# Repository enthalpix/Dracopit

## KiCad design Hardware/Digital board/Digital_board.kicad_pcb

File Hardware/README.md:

# Dracopit
74 logic custom interactive game

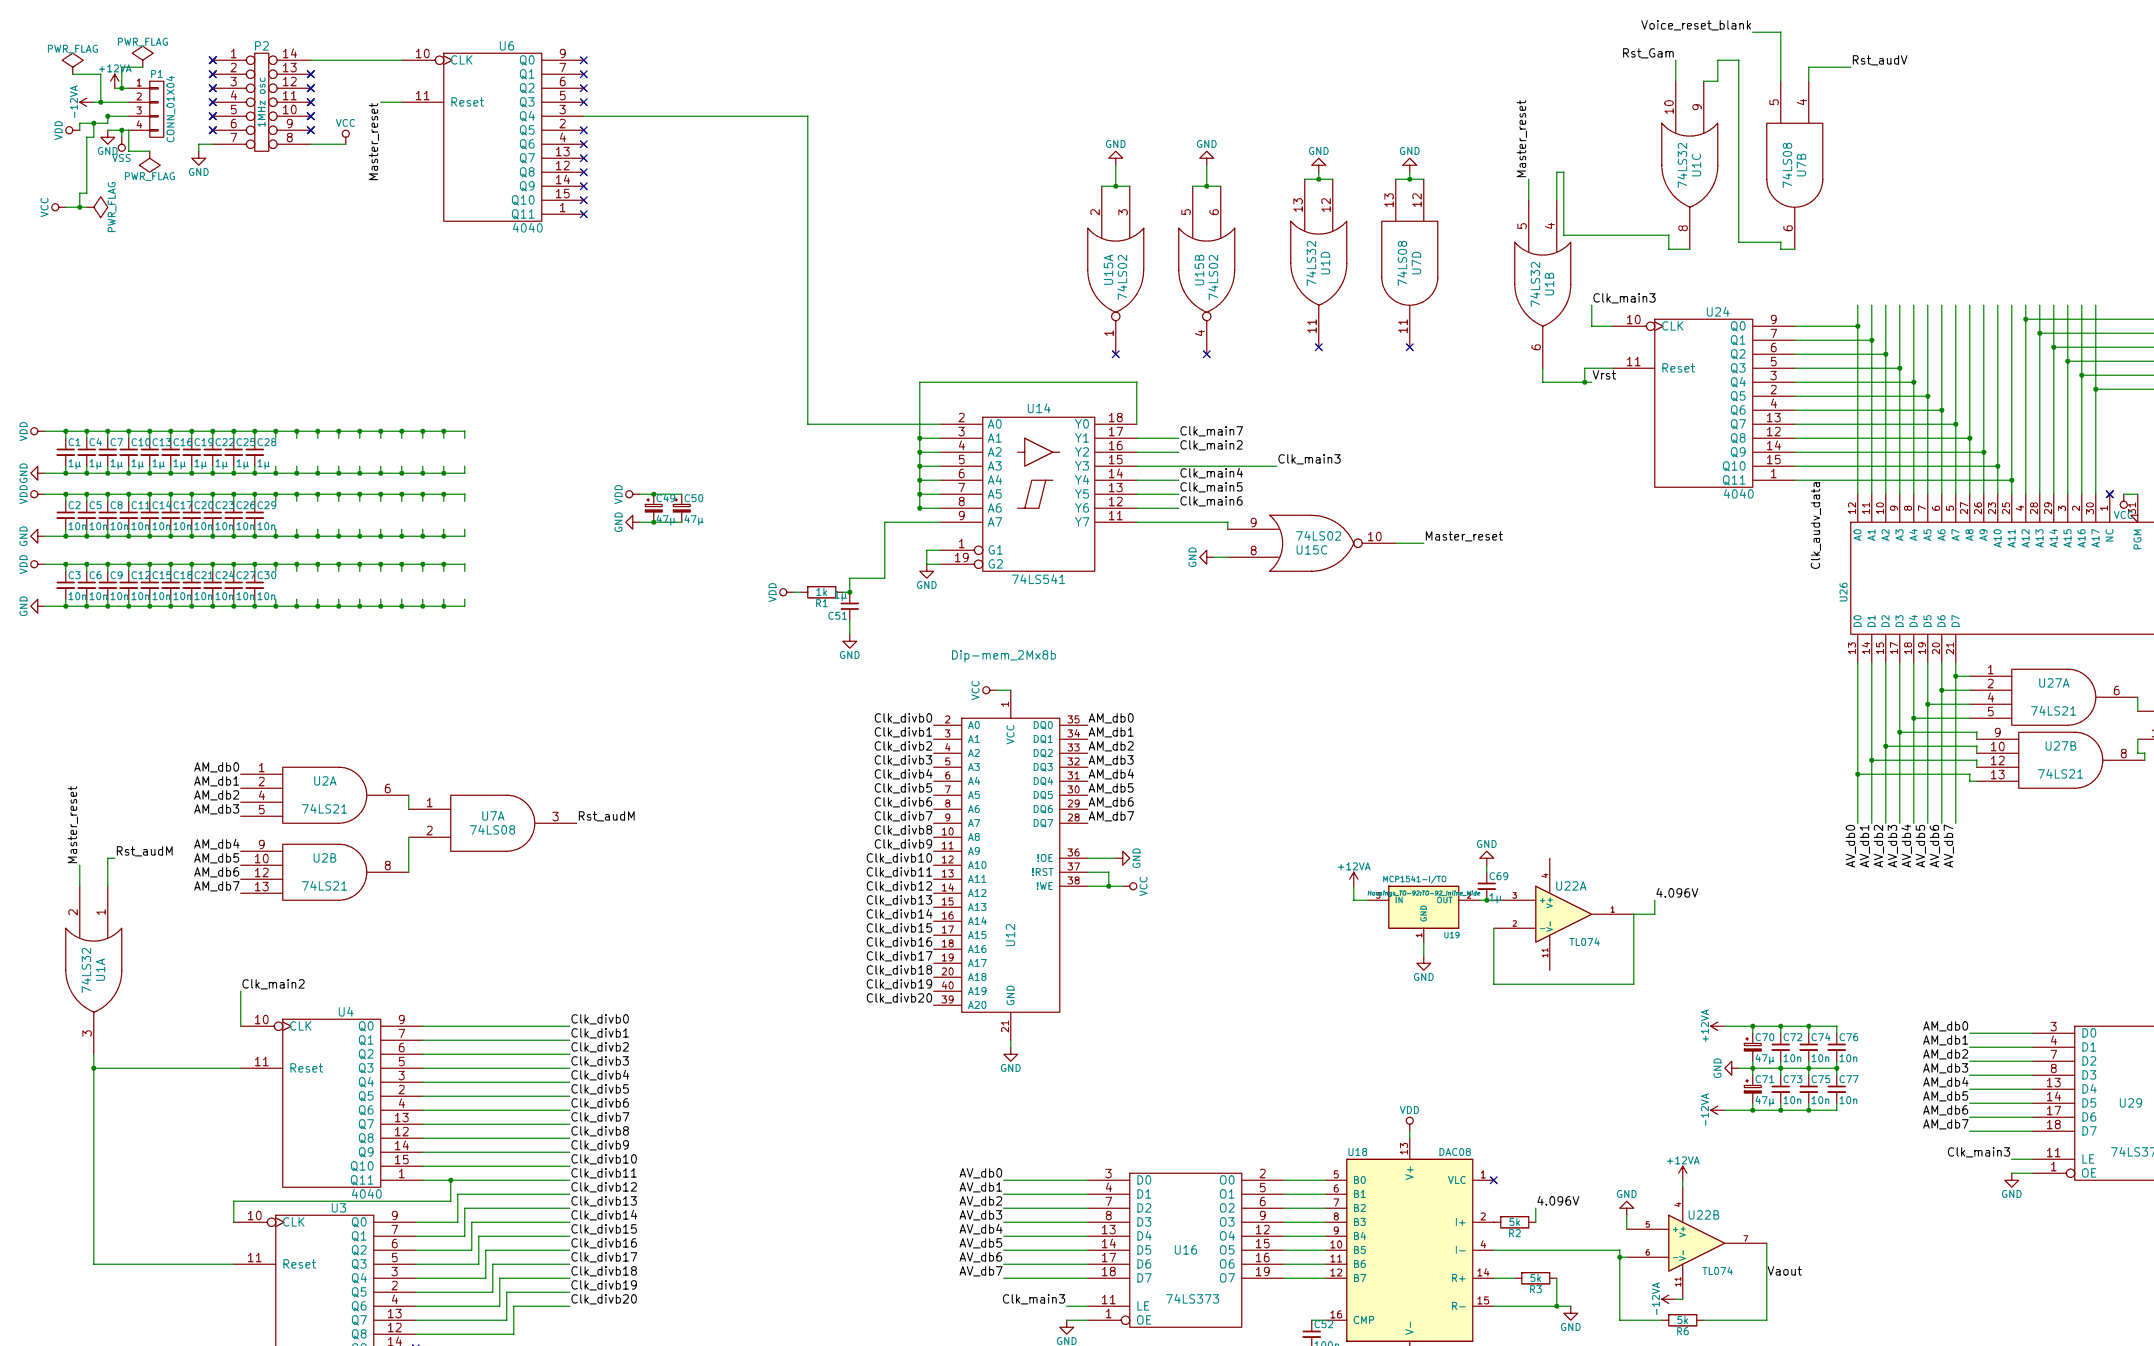
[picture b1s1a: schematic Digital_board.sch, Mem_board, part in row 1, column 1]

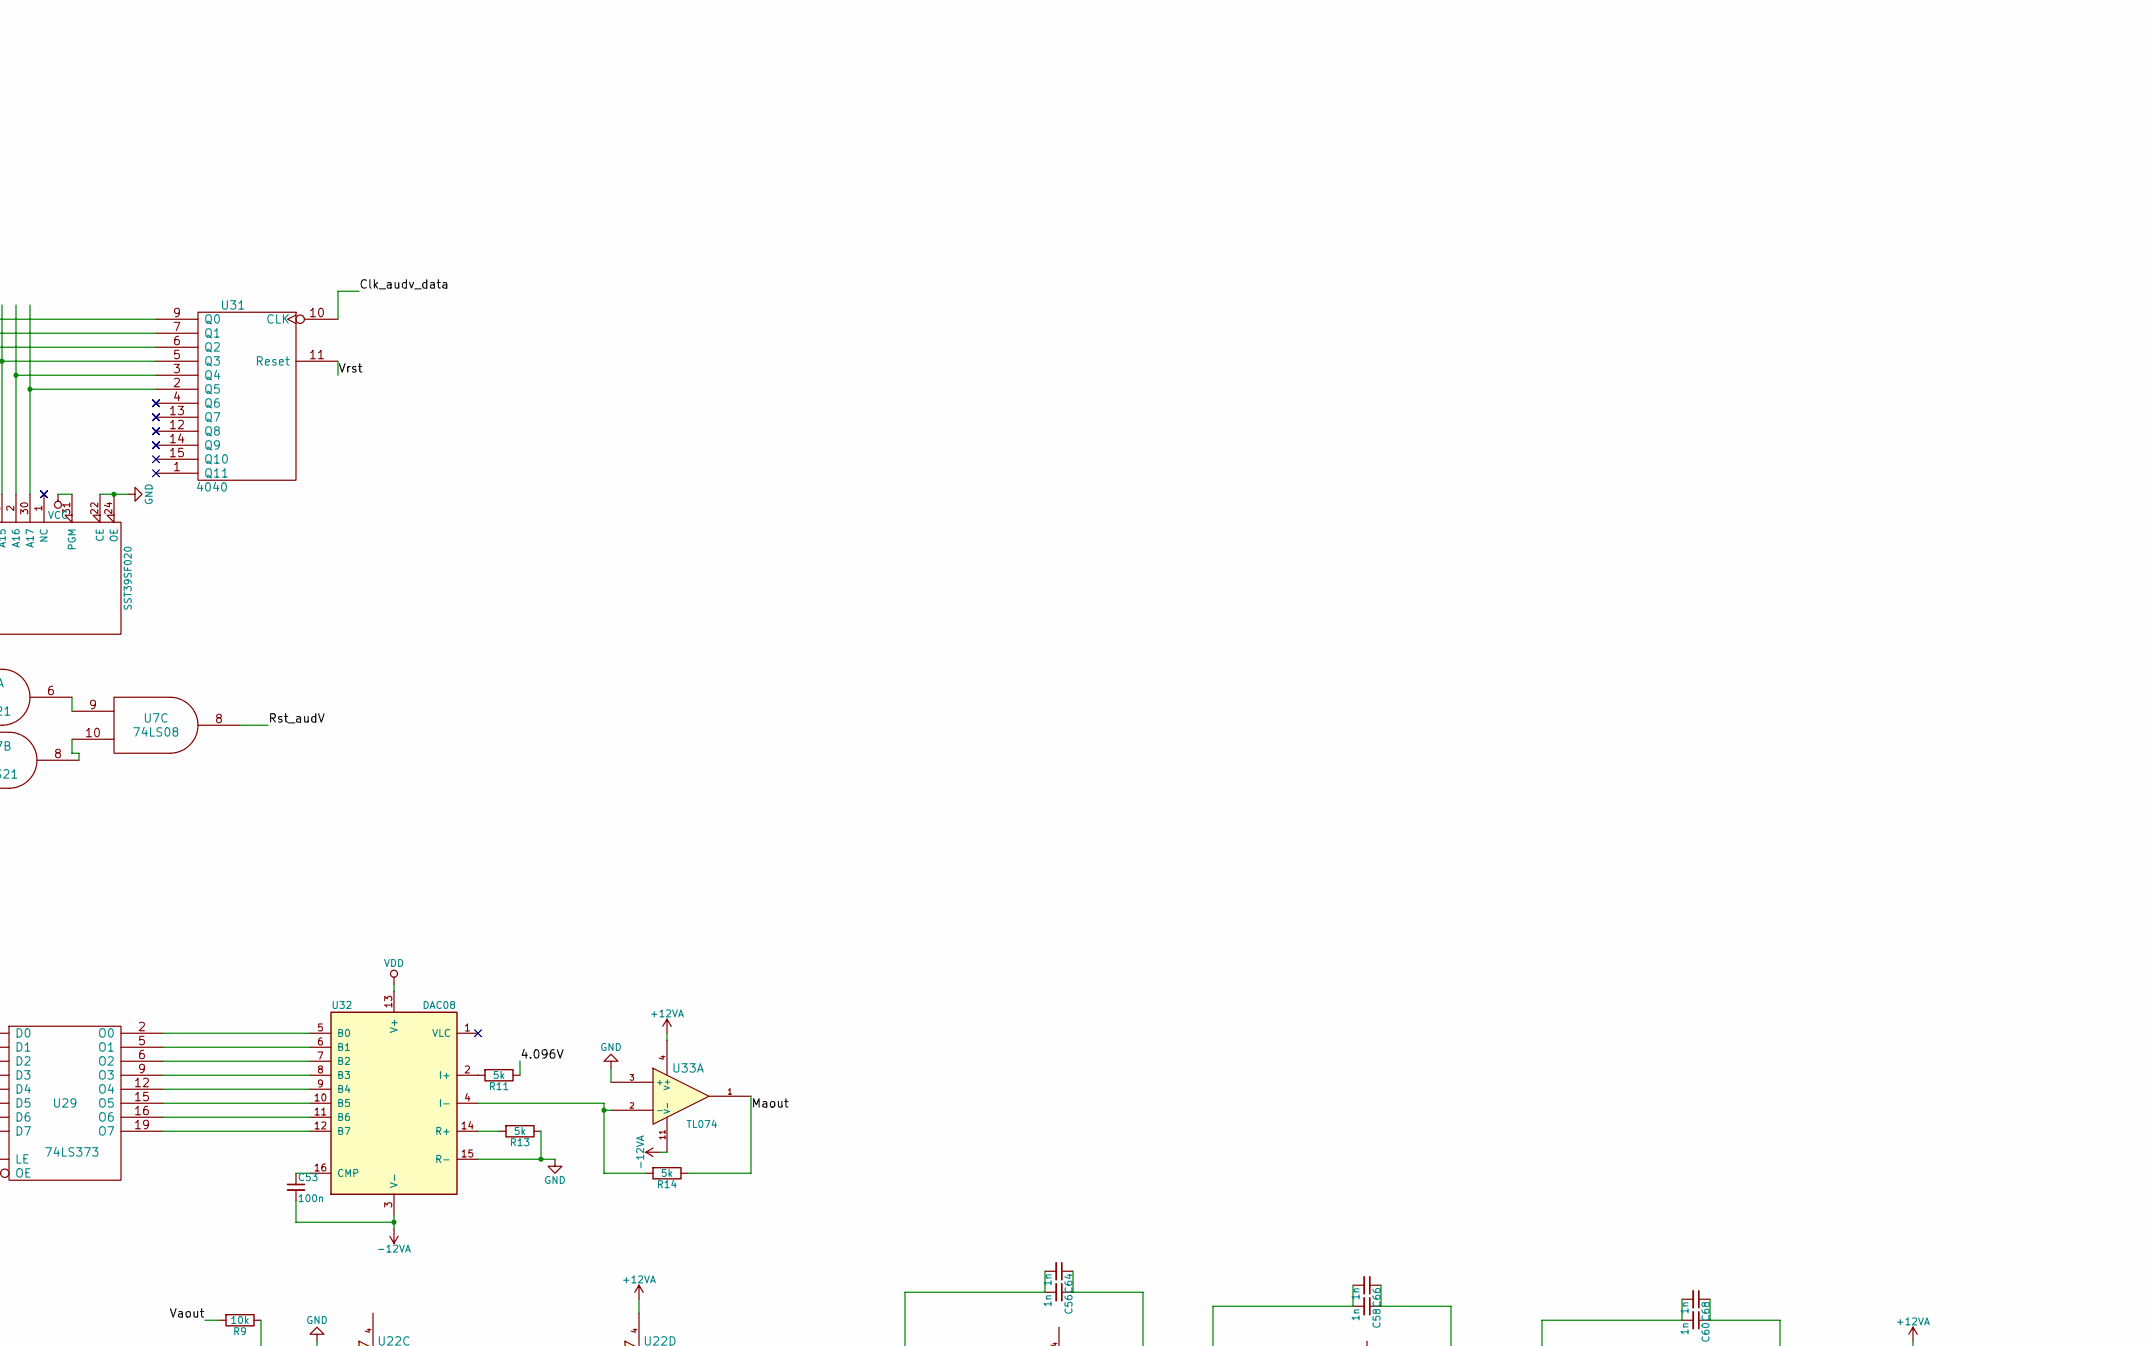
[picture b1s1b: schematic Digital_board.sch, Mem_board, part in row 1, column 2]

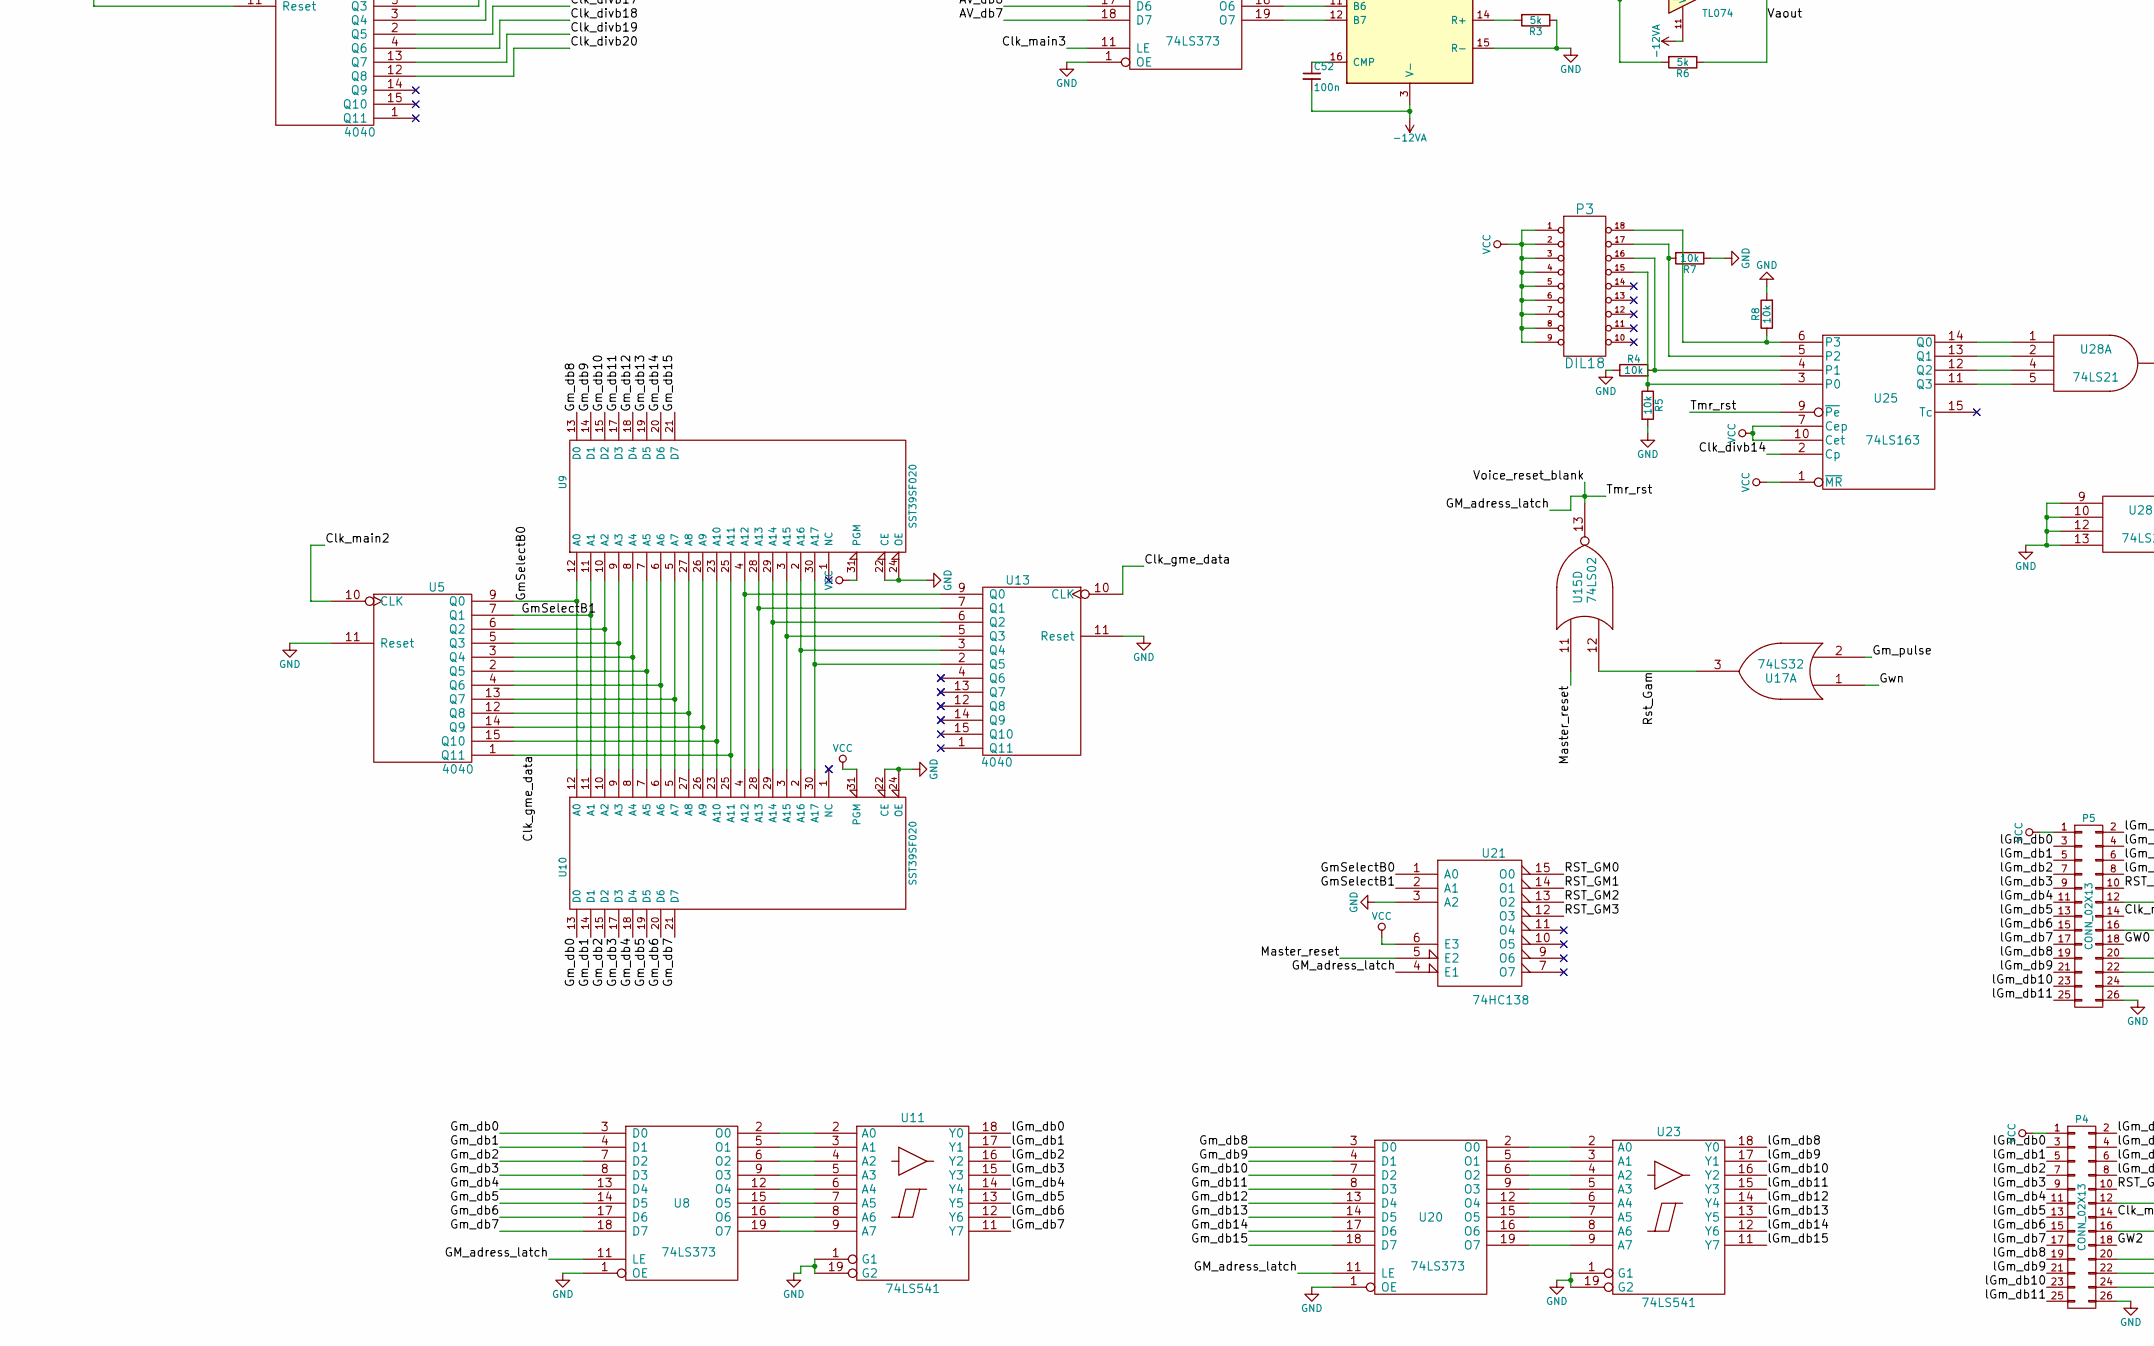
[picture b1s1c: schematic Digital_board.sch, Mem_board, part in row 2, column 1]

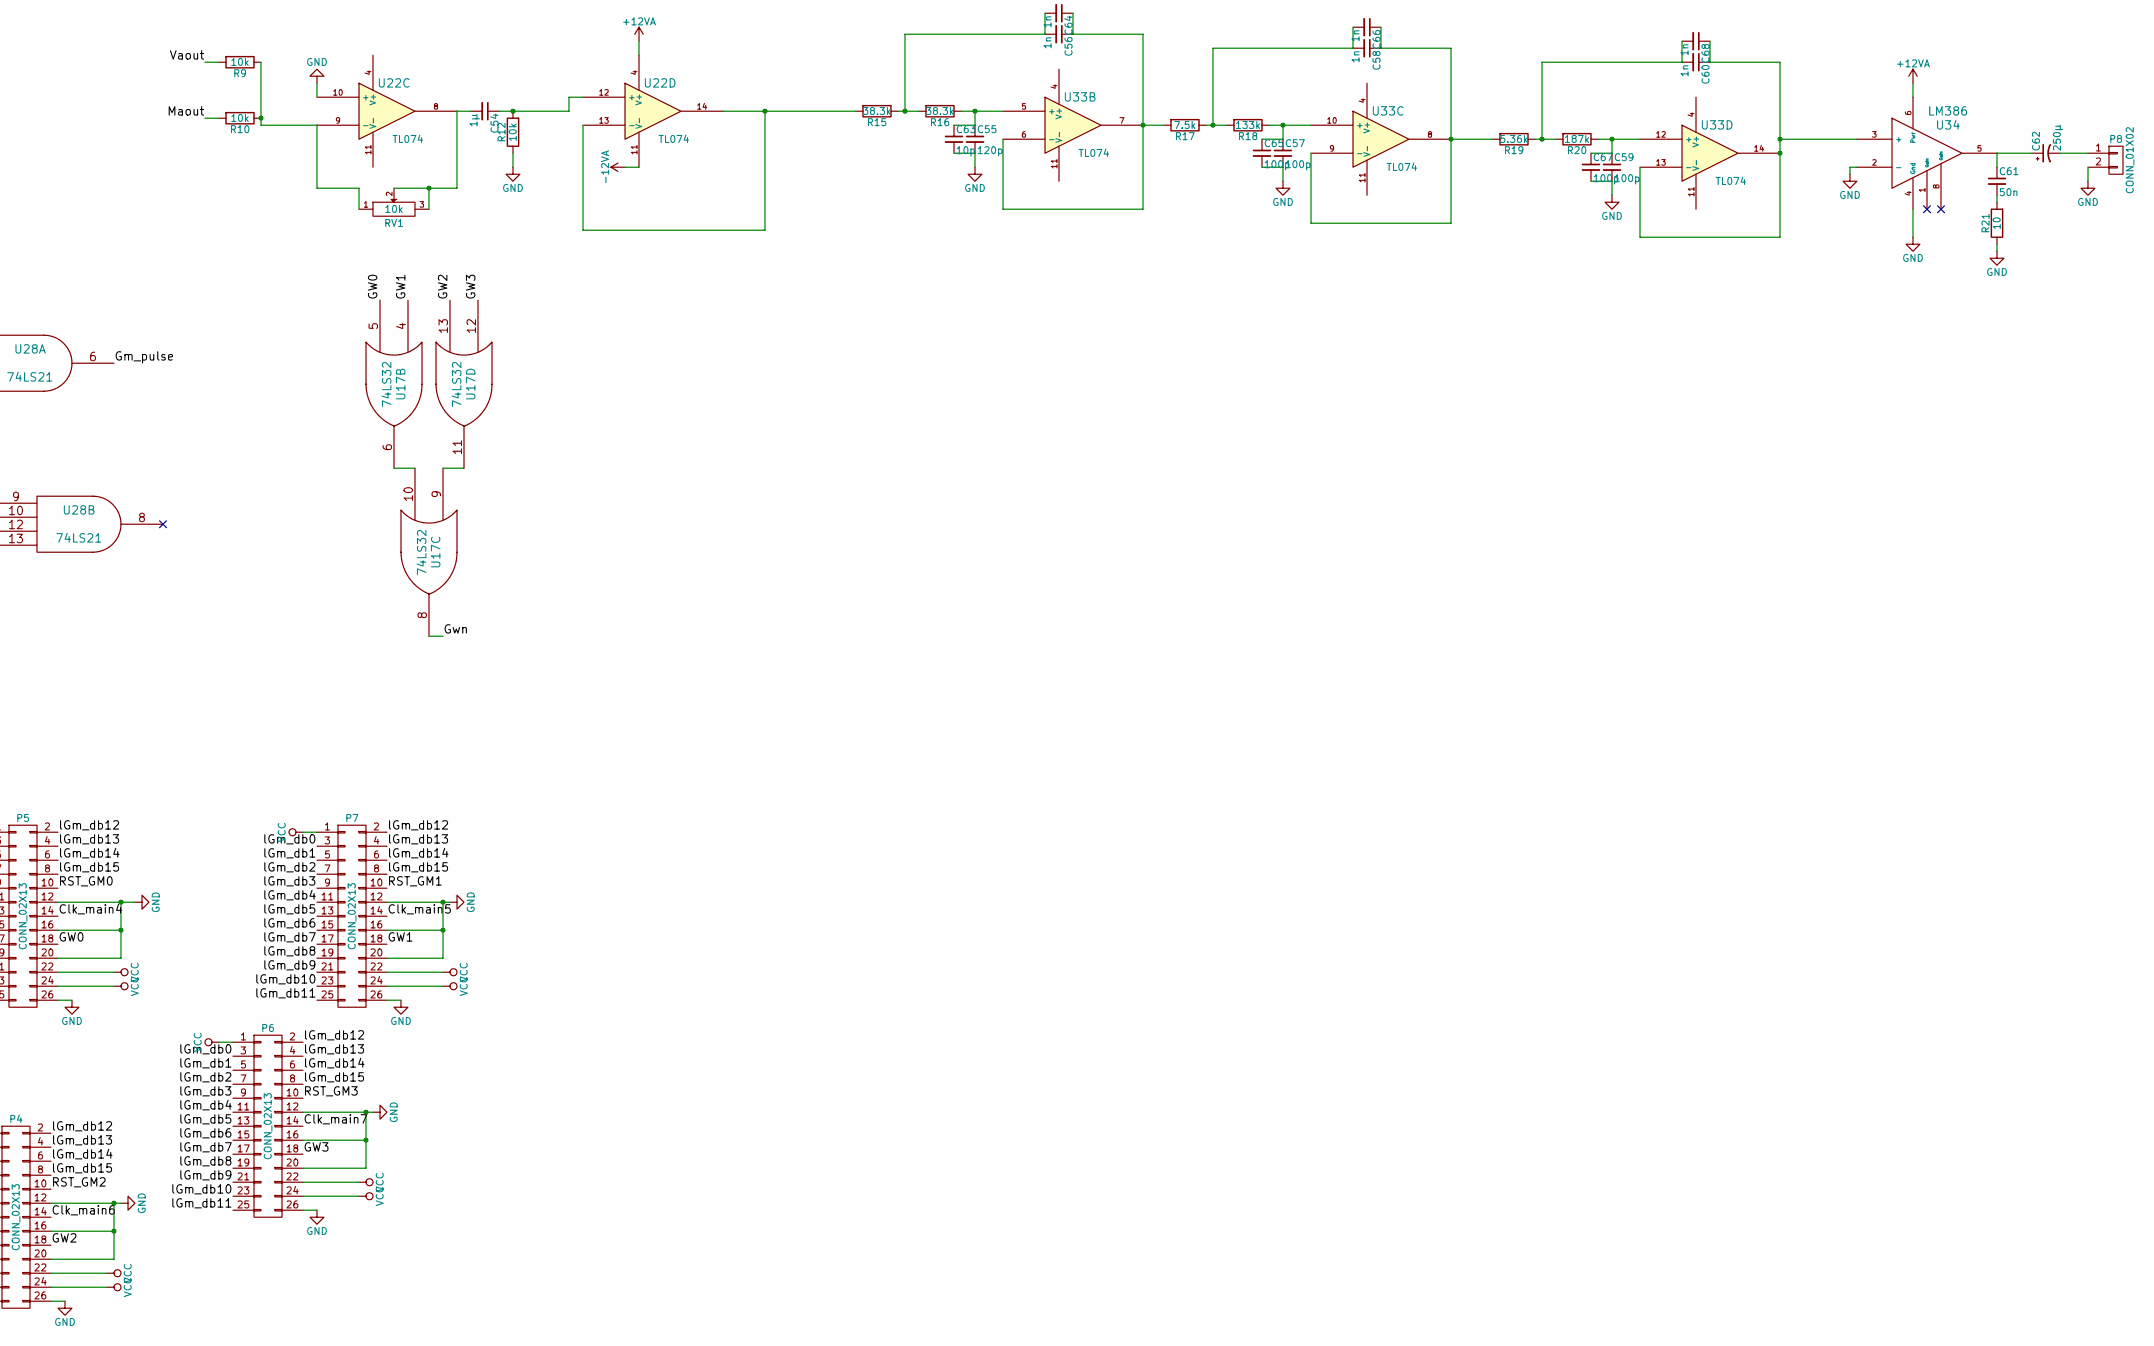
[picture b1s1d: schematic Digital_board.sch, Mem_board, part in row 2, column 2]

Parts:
C1, C4, C7, C10, C13, C16, C19, C22, C25, C28, C51, C54, C69: 1µ; C_0805_HandSoldering
C2, C3, C5, C6, C8, C9, C11, C12, C14, C15, C17, C18, C20, C21, C23, C24, C26, C27, C29, C30, C72, C73, C74, C75, C76, C77: 10n; C_0805_HandSoldering
C49, C70, C71: 47µ; c_elec_6.3x5.8
C50: 47µ; c_elec_6.3x5.7
C52, C53: 100n; C_0805_HandSoldering
C55: 120p; C_0805_HandSoldering
C56, C58, C60, C64, C66, C68: 1n; C_0805_HandSoldering
C57, C59, C65, C67: 100p; C_0805_HandSoldering
C61: 50n; C_0805_HandSoldering
C62: 250µ; c_elec_8x5.4
C63: 10p; C_0805_HandSoldering
P1: CONN_01X04; Socket_Strip_Straight_1x04
P2: 1MHz osc; DIP-14__300
P3: DIL18; DIP-18__300
P4, P5, P6, P7: CONN_02X13; Socket_Strip_Straight_2x13
P8: CONN_01X02; Socket_Strip_Angled_1x02
R1: 1k; R_0805_HandSoldering
R2, R3, R6, R11, R13, R14: 5k; R_0805_HandSoldering
R4, R5, R7, R8, R9, R10, R12: 10k; R_0805_HandSoldering
R15, R16: 38.3k; R_0805_HandSoldering
R17: 7.5k; R_0805_HandSoldering
R18: 133k; R_0805_HandSoldering
R19: 5.36k; R_0805_HandSoldering
R20: 187k; R_0805_HandSoldering
R21: 10; R_0805_HandSoldering
RV1: 10k; Potentiometer_WirePads_Small
U1, U17: 74LS32; DIP-14__300
U2, U27, U28: 74LS21; DIP-14__300
U3, U4, U5, U6, U13, U24, U31: 4040; DIP-16__300
U7: 74LS08; DIP-14__300
U8, U16, U20, U29: 74LS373; DIP-20__300
U9, U10, U26: SST39SF020; DIP-32__600
U11, U14, U23: 74LS541; DIP-20__300
U12: Dip-mem_2Mx8b; DIP-40__600
U15: 74LS02; DIP-14__300
U18, U32: DAC08; DIP-16__300
U19: MCP1541-I/TO; TO-92_Inline_Wide
U21: 74HC138; DIP-16__300
U22, U33: TL074; DIP-14__300
U25: 74LS163; DIP-16__300
U34: LM386; DIP-8__300

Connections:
+12VA: C70.1, C72.1, C74.1, C76.1, P1.1, U19.3 (IN), U22.4 (V+), U33.4 (V+), U34.6 (Pwr)
-12VA: C52.2, C53.2, C71.2, C73.2, C75.2, C77.2, P1.2, U18.3 (V-), U22.11 (V-), U32.3 (V-), U33.11 (V-)
/4.096V: R2.1, R11.1, U22.1, U22.2 (-)
/AM_db0: U2.1, U12.35 (DQ0), U29.3 (D0)
/AM_db1: U2.2, U12.34 (DQ1), U29.4 (D1)
/AM_db2: U2.4, U12.33 (DQ2), U29.7 (D2)
/AM_db3: U2.5, U12.32 (DQ3), U29.8 (D3)
/AM_db4: U2.9, U12.31 (DQ4), U29.13 (D4)
/AM_db5: U2.10, U12.30 (DQ5), U29.14 (D5)
/AM_db6: U2.12, U12.29 (DQ6), U29.17 (D6)
/AM_db7: U2.13, U12.28 (DQ7), U29.18 (D7)
/AV_db0: U16.3 (D0), U26.13 (D0), U27.13
/AV_db1: U16.4 (D1), U26.14 (D1), U27.12
/AV_db2: U16.7 (D2), U26.15 (D2), U27.10
/AV_db3: U16.8 (D3), U26.17 (D3), U27.9
/AV_db4: U16.13 (D4), U26.18 (D4), U27.5
/AV_db5: U16.14 (D5), U26.19 (D5), U27.4
/AV_db6: U16.17 (D6), U26.20 (D6), U27.2
/AV_db7: U16.18 (D7), U26.21 (D7), U27.1
/Clk_audv_data: U24.1 (Q11), U26.25 (A11), U31.10 (CLK)
/Clk_divb0: U4.9 (Q0), U12.2 (A0)
/Clk_divb1: U4.7 (Q1), U12.3 (A1)
/Clk_divb2: U4.6 (Q2), U12.4 (A2)
/Clk_divb3: U4.5 (Q3), U12.5 (A3)
/Clk_divb4: U4.3 (Q4), U12.6 (A4)
/Clk_divb5: U4.2 (Q5), U12.7 (A5)
/Clk_divb6: U4.4 (Q6), U12.8 (A6)
/Clk_divb7: U4.13 (Q7), U12.9 (A7)
/Clk_divb8: U4.12 (Q8), U12.10 (A8)
/Clk_divb9: U4.14 (Q9), U12.11 (A9)
/Clk_divb10: U4.15 (Q10), U12.12 (A10)
/Clk_divb11: U3.10 (CLK), U4.1 (Q11), U12.13 (A11)
/Clk_divb12: U3.9 (Q0), U12.14 (A12)
/Clk_divb13: U3.7 (Q1), U12.15 (A13)
/Clk_divb14: U3.6 (Q2), U12.16 (A14), U25.2 (Cp)
/Clk_divb15: U3.5 (Q3), U12.17 (A15)
/Clk_divb16: U3.3 (Q4), U12.18 (A16)
/Clk_divb17: U3.2 (Q5), U12.19 (A17)
/Clk_divb18: U3.4 (Q6), U12.20 (A18)
/Clk_divb19: U3.13 (Q7), U12.40 (A19)
/Clk_divb20: U3.12 (Q8), U12.39 (A20)
/Clk_gme_data: U5.1 (Q11), U9.25 (A11), U10.25 (A11), U13.10 (CLK)
/Clk_main2: U4.10 (CLK), U5.10 (CLK), U14.16 (Y2)
/Clk_main3: U14.15 (Y3), U16.11 (LE), U24.10 (CLK), U29.11 (LE)
/Clk_main4: P5.14, U14.14 (Y4)
/Clk_main5: P7.14, U14.13 (Y5)
/Clk_main6: P4.14, U14.12 (Y6)
/Clk_main7: P6.14, U14.17 (Y1)
/GM_adress_latch: U7.5, U8.11 (LE), U15.13, U20.11 (LE), U21.4 (E1), U25.9 (~Pe)
/GW0: P5.18, U17.5
/GW1: P7.18, U17.4
/GW2: P4.18, U17.13
/GW3: P6.18, U17.12
/GmSelectB0: U5.9 (Q0), U9.12 (A0), U10.12 (A0), U21.1 (A0)
/GmSelectB1: U5.7 (Q1), U9.11 (A1), U10.11 (A1), U21.2 (A1)
/Gm_db0: U8.3 (D0), U10.13 (D0)
/Gm_db1: U8.4 (D1), U10.14 (D1)
/Gm_db2: U8.7 (D2), U10.15 (D2)
/Gm_db3: U8.8 (D3), U10.17 (D3)
/Gm_db4: U8.13 (D4), U10.18 (D4)
/Gm_db5: U8.14 (D5), U10.19 (D5)
/Gm_db6: U8.17 (D6), U10.20 (D6)
/Gm_db7: U8.18 (D7), U10.21 (D7)
/Gm_db8: U9.13 (D0), U20.3 (D0)
/Gm_db9: U9.14 (D1), U20.4 (D1)
/Gm_db10: U9.15 (D2), U20.7 (D2)
/Gm_db11: U9.17 (D3), U20.8 (D3)
/Gm_db12: U9.18 (D4), U20.13 (D4)
/Gm_db13: U9.19 (D5), U20.14 (D5)
/Gm_db14: U9.20 (D6), U20.17 (D6)
/Gm_db15: U9.21 (D7), U20.18 (D7)
/Gm_pulse: U17.2, U28.6
/Gwn: U17.1, U17.8
/Maout: R10.2, R14.1, U33.1
/Master_reset: U1.2, U1.5, U6.11 (Reset), U15.10, U15.11, U21.5 (E2)
/RST_GM0: P5.10, U21.15 (O0)
/RST_GM1: P7.10, U21.14 (O1)
/RST_GM2: P4.10, U21.13 (O2)
/RST_GM3: P6.10, U21.12 (O3)
/Rst_Gam: U1.10, U15.12, U17.3
/Rst_audM: U1.1, U7.3
/Rst_audV: U7.4, U7.8
/Vaout: R6.1, R9.2, U22.7
/Vrst: U1.6, U24.11 (Reset), U31.11 (Reset)
/lGm_db0: P4.3, P5.3, P6.3, P7.3, U11.18 (Y0)
/lGm_db1: P4.5, P5.5, P6.5, P7.5, U11.17 (Y1)
/lGm_db2: P4.7, P5.7, P6.7, P7.7, U11.16 (Y2)
/lGm_db3: P4.9, P5.9, P6.9, P7.9, U11.15 (Y3)
/lGm_db4: P4.11, P5.11, P6.11, P7.11, U11.14 (Y4)
/lGm_db5: P4.13, P5.13, P6.13, P7.13, U11.13 (Y5)
/lGm_db6: P4.15, P5.15, P6.15, P7.15, U11.12 (Y6)
/lGm_db7: P4.17, P5.17, P6.17, P7.17, U11.11 (Y7)
/lGm_db8: P4.19, P5.19, P6.19, P7.19, U23.18 (Y0)
/lGm_db9: P4.21, P5.21, P6.21, P7.21, U23.17 (Y1)
/lGm_db10: P4.23, P5.23, P6.23, P7.23, U23.16 (Y2)
/lGm_db11: P4.25, P5.25, P6.25, P7.25, U23.15 (Y3)
/lGm_db12: P4.2, P5.2, P6.2, P7.2, U23.14 (Y4)
/lGm_db13: P4.4, P5.4, P6.4, P7.4, U23.13 (Y5)
/lGm_db14: P4.6, P5.6, P6.6, P7.6, U23.12 (Y6)
/lGm_db15: P4.8, P5.8, P6.8, P7.8, U23.11 (Y7)
GND: C1.2, C2.2, C3.2, C4.2, C5.2, C6.2, C7.2, C8.2, C9.2, C10.2, C11.2, C12.2, C13.2, C14.2, C15.2, C16.2, C17.2, C18.2, C19.2, C20.2, C21.2, C22.2, C23.2, C24.2, C25.2, C26.2, C27.2, C28.2, C29.2, C30.2, C49.2, C50.2, C51.1, C55.2, C57.2, C59.2, C63.2, C65.2, C67.2, C69.1, C70.2, C71.1, C72.2, C73.1, C74.2, C75.1, C76.2, C77.1, P1.4, P2.7, P4.12, P4.16, P4.20, P4.26, P5.12, P5.16, P5.20, P5.26, P6.12, P6.16, P6.20, P6.26, P7.12, P7.16, P7.20, P7.26, P8.2, R3.1, R4.1, R5.2, R7.1, R8.2, R12.1, R13.1, R21.1, U1.7 (GND), U1.12, U1.13, U2.7 (GND), U3.8 (VSS), U4.8 (VSS), U5.8 (VSS), U5.11 (Reset), U6.8 (VSS), U7.7 (GND), U7.12, U7.13, U8.1 (OE), U8.10 (GND), U9.16 (GND), U9.22 (CE), U9.24 (OE), U10.16 (GND), U10.22 (CE), U10.24 (OE), U11.1 (G1), U11.10 (GND), U11.19 (G2), U12.21 (GND), U12.36 (!OE), U13.8 (VSS), U13.11 (Reset), U14.1 (G1), U14.10 (GND), U14.19 (G2), U15.2, U15.3, U15.5, U15.6, U15.7 (GND), U15.8, U16.1 (OE), U16.10 (GND), U17.7 (GND), U18.15 (R-), U19.1 (GND), U20.1 (OE), U20.10 (GND), U21.3 (A2), U21.8 (GND), U22.5 (+), U22.10 (+), U23.1 (G1), U23.10 (GND), U23.19 (G2), U24.8 (VSS), U25.8 (GND), U26.16 (GND), U26.22 (CE), U26.24 (OE), U27.7 (GND), U28.7 (GND), U28.9, U28.10, U28.12, U28.13, U29.1 (OE), U29.10 (GND), U31.8 (VSS), U32.15 (R-), U33.3 (+), U34.2 (-), U34.4 (Gnd)
unnamed: C51.2, R1.1, U14.9 (A7)
unnamed: C52.1, U18.16 (CMP)
unnamed: C53.1, U32.16 (CMP)
unnamed: C54.1, R12.2, U22.12 (+)
unnamed: C54.2, RV1.2, RV1.3, U22.8
unnamed: C55.1, C63.1, R16.1, U33.5 (+)
unnamed: C56.1, C64.1, R17.2, U33.6 (-), U33.7
unnamed: C56.2, C64.2, R15.1, R16.2
unnamed: C57.1, C65.1, R18.1, U33.10 (+)
unnamed: C58.1, C66.1, R19.2, U33.8, U33.9 (-)
unnamed: C58.2, C66.2, R17.1, R18.2
unnamed: C59.1, C67.1, R20.1, U33.12 (+)
unnamed: C60.1, C68.1, U33.13 (-), U33.14, U34.3 (+)
unnamed: C60.2, C68.2, R19.1, R20.2
unnamed: C61.1, C62.1, U34.5
unnamed: C61.2, R21.2
unnamed: C62.2, P8.1
unnamed: C69.2, U19.2 (OUT), U22.3 (+)
unnamed: P2.14, U6.10 (CLK)
unnamed: P3.15, R5.1, U25.3 (P0)
unnamed: P3.16, R4.2, U25.4 (P1)
unnamed: P3.17, R7.2, U25.5 (P2)
unnamed: P3.18, R8.1, U25.6 (P3)
unnamed: R2.2, U18.2 (I+)
unnamed: R3.2, U18.14 (R+)
unnamed: R6.2, U18.4 (I-), U22.6 (-)
unnamed: R9.1, R10.1, RV1.1, U22.9 (-)
unnamed: R11.2, U32.2 (I+)
unnamed: R13.2, U32.14 (R+)
unnamed: R14.2, U32.4 (I-), U33.2 (-)
unnamed: R15.2, U22.13 (-), U22.14
unnamed: U1.3, U3.11 (Reset), U4.11 (Reset)
unnamed: U1.4, U1.8
unnamed: U1.9, U7.6
unnamed: U2.6, U7.1
unnamed: U2.8, U7.2
unnamed: U9.2 (A16), U10.2 (A16), U13.3 (Q4)
unnamed: U9.3 (A15), U10.3 (A15), U13.5 (Q3)
unnamed: U9.4 (A12), U10.4 (A12), U13.9 (Q0)
unnamed: U5.13 (Q7), U9.5 (A7), U10.5 (A7)
unnamed: U5.4 (Q6), U9.6 (A6), U10.6 (A6)
unnamed: U5.2 (Q5), U9.7 (A5), U10.7 (A5)
unnamed: U5.3 (Q4), U9.8 (A4), U10.8 (A4)
unnamed: U5.5 (Q3), U9.9 (A3), U10.9 (A3)
unnamed: U5.6 (Q2), U9.10 (A2), U10.10 (A2)
unnamed: U5.15 (Q10), U9.23 (A10), U10.23 (A10)
unnamed: U5.14 (Q9), U9.26 (A9), U10.26 (A9)
unnamed: U5.12 (Q8), U9.27 (A8), U10.27 (A8)
unnamed: U9.28 (A13), U10.28 (A13), U13.7 (Q1)
unnamed: U9.29 (A14), U10.29 (A14), U13.6 (Q2)
unnamed: U9.30 (A17), U10.30 (A17), U13.2 (Q5)
unnamed: U8.2 (O0), U11.2 (A0)
unnamed: U8.5 (O1), U11.3 (A1)
unnamed: U8.6 (O2), U11.4 (A2)
unnamed: U8.9 (O3), U11.5 (A3)
unnamed: U8.12 (O4), U11.6 (A4)
unnamed: U8.15 (O5), U11.7 (A5)
unnamed: U8.16 (O6), U11.8 (A6)
unnamed: U8.19 (O7), U11.9 (A7)
unnamed: U6.3 (Q4), U14.2 (A0)
unnamed: U14.11 (Y7), U15.9
unnamed: U14.3 (A1), U14.4 (A2), U14.5 (A3), U14.6 (A4), U14.7 (A5), U14.8 (A6), U14.18 (Y0)
unnamed: U16.2 (O0), U18.5 (B0)
unnamed: U16.5 (O1), U18.6 (B1)
unnamed: U16.6 (O2), U18.7 (B2)
unnamed: U16.9 (O3), U18.8 (B3)
unnamed: U16.12 (O4), U18.9 (B4)
unnamed: U16.15 (O5), U18.10 (B5)
unnamed: U16.16 (O6), U18.11 (B6)
unnamed: U16.19 (O7), U18.12 (B7)
unnamed: U17.6, U17.10
unnamed: U17.9, U17.11
unnamed: U20.2 (O0), U23.2 (A0)
unnamed: U20.5 (O1), U23.3 (A1)
unnamed: U20.6 (O2), U23.4 (A2)
unnamed: U20.9 (O3), U23.5 (A3)
unnamed: U20.12 (O4), U23.6 (A4)
unnamed: U20.15 (O5), U23.7 (A5)
unnamed: U20.16 (O6), U23.8 (A6)
unnamed: U20.19 (O7), U23.9 (A7)
unnamed: U24.2 (Q5), U26.7 (A5)
unnamed: U24.3 (Q4), U26.8 (A4)
unnamed: U24.4 (Q6), U26.6 (A6)
unnamed: U24.5 (Q3), U26.9 (A3)
unnamed: U24.6 (Q2), U26.10 (A2)
unnamed: U24.7 (Q1), U26.11 (A1)
unnamed: U24.9 (Q0), U26.12 (A0)
unnamed: U24.12 (Q8), U26.27 (A8)
unnamed: U24.13 (Q7), U26.5 (A7)
unnamed: U24.14 (Q9), U26.26 (A9)
unnamed: U24.15 (Q10), U26.23 (A10)
unnamed: U25.11 (Q3), U28.5
unnamed: U25.12 (Q2), U28.4
unnamed: U25.13 (Q1), U28.2
unnamed: U25.14 (Q0), U28.1
unnamed: U26.2 (A16), U31.3 (Q4)
unnamed: U26.3 (A15), U31.5 (Q3)
unnamed: U26.4 (A12), U31.9 (Q0)
unnamed: U26.28 (A13), U31.7 (Q1)
unnamed: U26.29 (A14), U31.6 (Q2)
unnamed: U26.30 (A17), U31.2 (Q5)
unnamed: U7.9, U27.6
unnamed: U7.10, U27.8
unnamed: U29.2 (O0), U32.5 (B0)
unnamed: U29.5 (O1), U32.6 (B1)
unnamed: U29.6 (O2), U32.7 (B2)
unnamed: U29.9 (O3), U32.8 (B3)
unnamed: U29.12 (O4), U32.9 (B4)
unnamed: U29.15 (O5), U32.10 (B5)
unnamed: U29.16 (O6), U32.11 (B6)
unnamed: U29.19 (O7), U32.12 (B7)
VCC: C1.1, C2.1, C3.1, C4.1, C5.1, C6.1, C7.1, C8.1, C9.1, C10.1, C11.1, C12.1, C13.1, C14.1, C15.1, C16.1, C17.1, C18.1, C19.1, C20.1, C21.1, C22.1, C23.1, C24.1, C25.1, C26.1, C27.1, C28.1, C29.1, C30.1, C49.1, C50.1, P1.3, P2.8, P3.1, P3.2, P3.3, P3.4, P3.5, P3.6, P3.7, P3.8, P3.9, P4.1, P4.22, P4.24, P5.1, P5.22, P5.24, P6.1, P6.22, P6.24, P7.1, P7.22, P7.24, R1.2, U1.14 (VCC), U2.14 (VCC), U3.16 (VDD), U4.16 (VDD), U5.16 (VDD), U6.16 (VDD), U7.14 (VCC), U8.20 (VCC), U9.31 (PGM), U9.32 (VCC), U10.31 (PGM), U10.32 (VCC), U11.20 (VCC), U12.1 (VCC), U12.37 (!RST), U12.38 (!WE), U13.16 (VDD), U14.20 (VCC), U15.14 (VCC), U16.20 (VCC), U17.14 (VCC), U18.13 (V+), U20.20 (VCC), U21.6 (E3), U21.16 (VCC), U23.20 (VCC), U24.16 (VDD), U25.1 (~MR), U25.7 (Cep), U25.10 (Cet), U25.16 (VCC), U26.31 (PGM), U26.32 (VCC), U27.14 (VCC), U28.14 (VCC), U29.20 (VCC), U31.16 (VDD), U32.13 (V+)

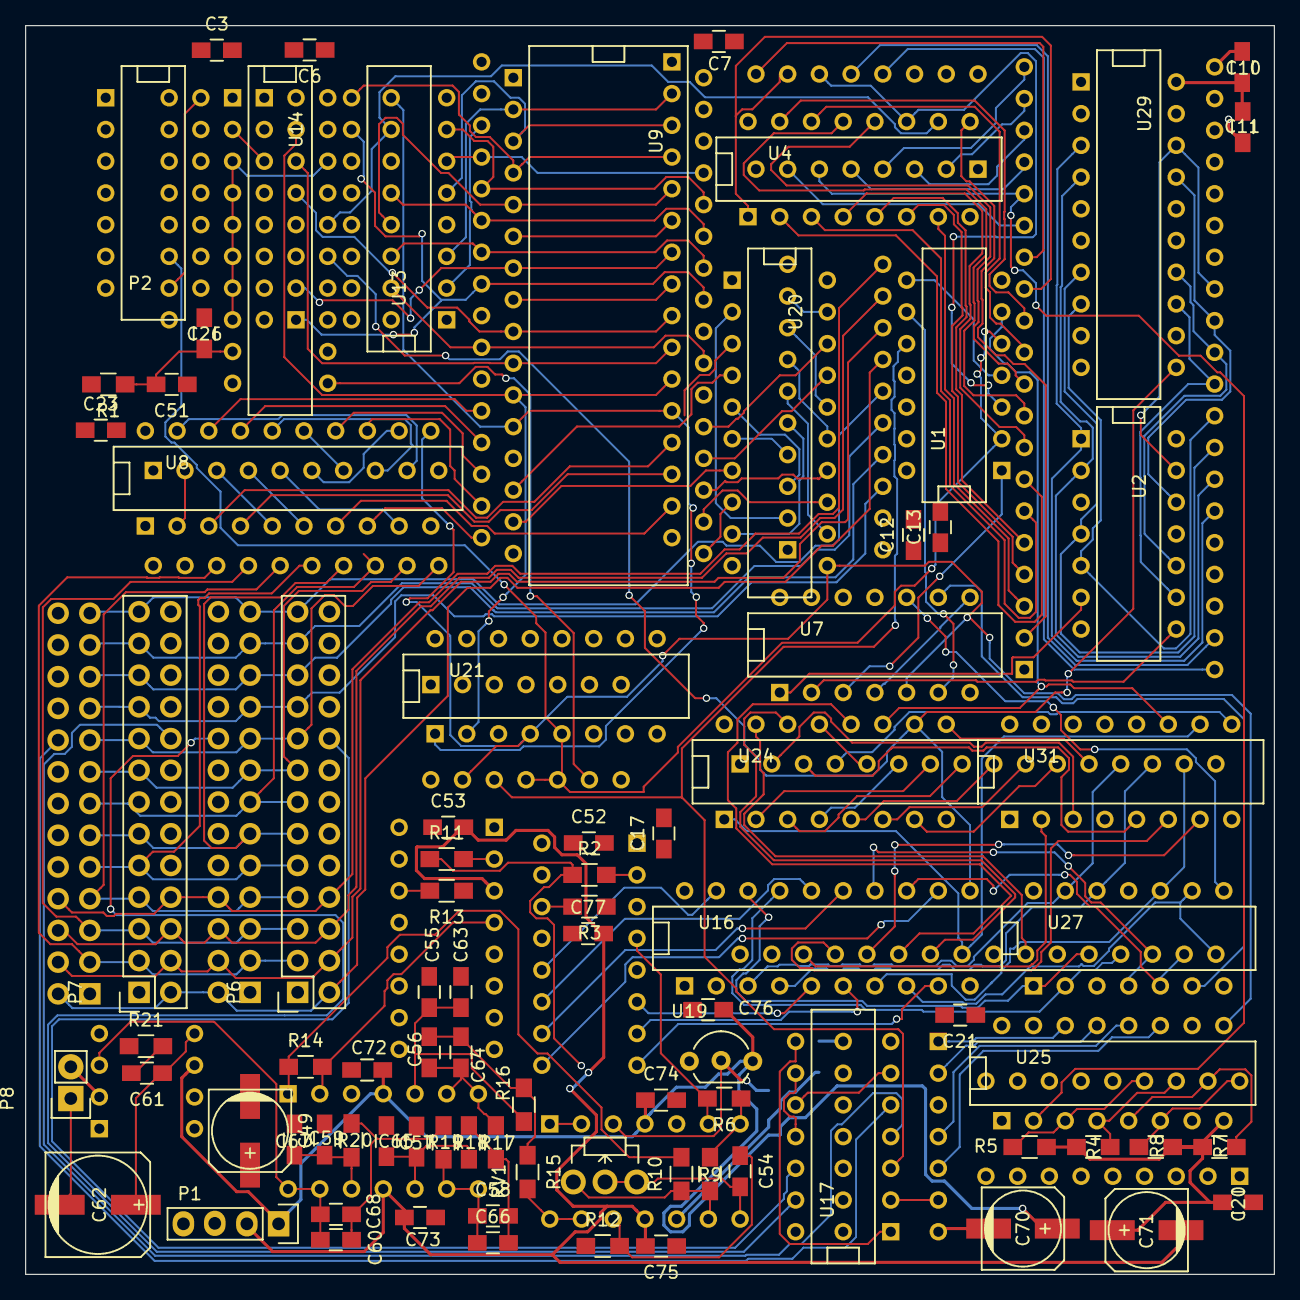
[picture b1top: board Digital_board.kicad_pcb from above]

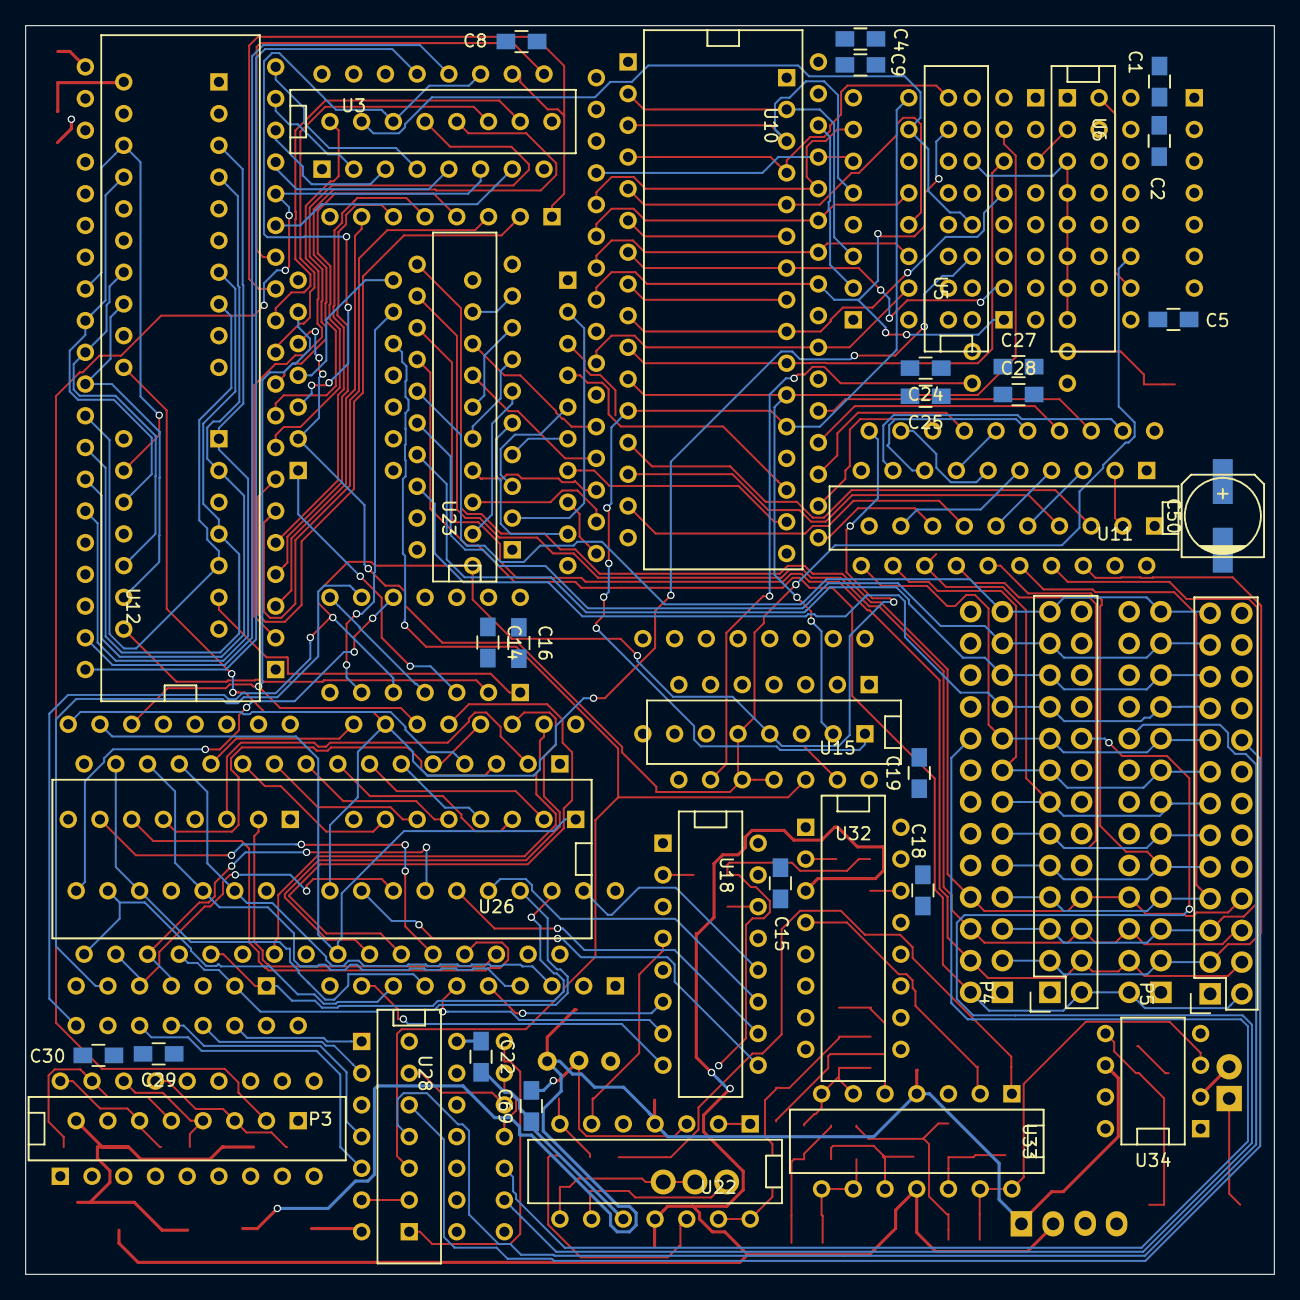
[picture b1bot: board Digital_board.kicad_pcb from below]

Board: 4 copper layers, 100.0 x 100.0 mm, 122 parts (38 on the bottom side), 213 nets.
